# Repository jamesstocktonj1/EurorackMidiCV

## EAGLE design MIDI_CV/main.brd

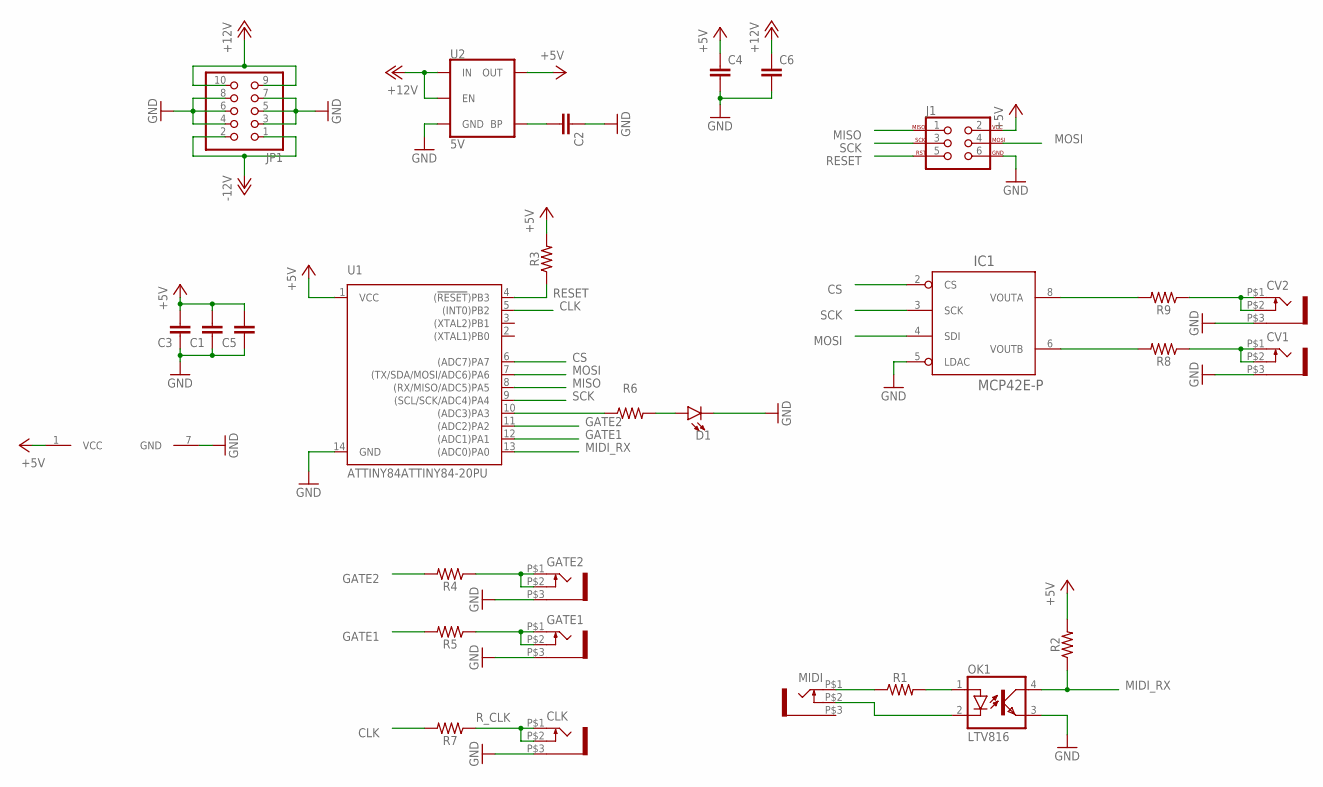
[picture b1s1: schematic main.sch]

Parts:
C1, C2, C3, C5: CAP-0603; 0603
C4, C6: CAP-0805; 0805
CLK: WQP-PJ301M-12_JACK
CV1, CV2: WQP-PJ301M-12_JACK
D1: LED3MM; LED_3MM
GATE1, GATE2: WQP-PJ301M-12_JACK
IC1: MCP42E-P; DIL08
J1: AVR_SPI_PROG_3X2PTH; 2X3
JP1: PINHD-2X5; 2X05
MIDI: WQP-PJ301M-12_JACK
OK1: LTV816; DIL04
R1, R2: AXIAL-0.3
R3, R4, R5, R6, R7, R8, R9: 0603
U1: ATTINY84ATTINY84-20PU; DIP14
U2: 5V; SOT23-5

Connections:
+5V: C1.2, C3.2, C4.1, C5.2, IC1.1 (VCC), J1.2, R2.P$2 (2), R3.2, U1.1 (VCC), U2.5 (OUT)
+12V: C6.1, JP1.9, JP1.10, U2.1 (IN), U2.3 (EN)
-12V: JP1.1, JP1.2
CLK: R7.2, U1.5 ((INT0)PB2)
CS: IC1.2 (CS), U1.6 ((ADC7)PA7)
GATE1: R5.2, U1.12 ((ADC1)PA1)
GATE2: R4.2, U1.11 ((ADC2)PA2)
GND: C1.1, C2.1, C3.1, C4.2, C5.1, C6.2, CLK.P$3 (1), CV1.P$3 (1), CV2.P$3 (1), D1.K (C), GATE1.P$3 (1), GATE2.P$3 (1), IC1.5 (LDAC), IC1.7 (GND), J1.6, JP1.3, JP1.4, JP1.5, JP1.6, JP1.7, JP1.8, OK1.3 (EMIT), U1.14 (GND), U2.2 (GND)
MIDI_RX: OK1.4 (COL), R2.P$1 (1), U1.13 ((ADC0)PA0)
MISO: J1.1, U1.8 ((RX/MISO/ADC5)PA5)
MOSI: IC1.4 (SDI), J1.4, U1.7 ((TX/SDA/MOSI/ADC6)PA6)
unnamed: MIDI.P$1 (2), R1.P$1 (1)
unnamed: OK1.1 (A), R1.P$2 (2)
unnamed: MIDI.P$2 (3), OK1.2 (C)
unnamed: IC1.8 (VOUTA), R9.2
unnamed: IC1.6 (VOUTB), R8.2
unnamed: CV1.P$1 (2), CV1.P$2 (3), R8.1
unnamed: R6.1, U1.10 ((ADC3)PA3)
unnamed: D1.A, R6.2
unnamed: C2.2, U2.4 (BP)
unnamed: CV2.P$1 (2), CV2.P$2 (3), R9.1
RESET: J1.5, R3.1, U1.4 ((!RESET!)PB3)
R_CLK: CLK.P$1 (2), CLK.P$2 (3), R7.1
R_GATE1: GATE1.P$1 (2), GATE1.P$2 (3), R5.1
R_GATE2: GATE2.P$1 (2), GATE2.P$2 (3), R4.1
SCK: IC1.3 (SCK), J1.3, U1.9 ((SCL/SCK/ADC4)PA4)

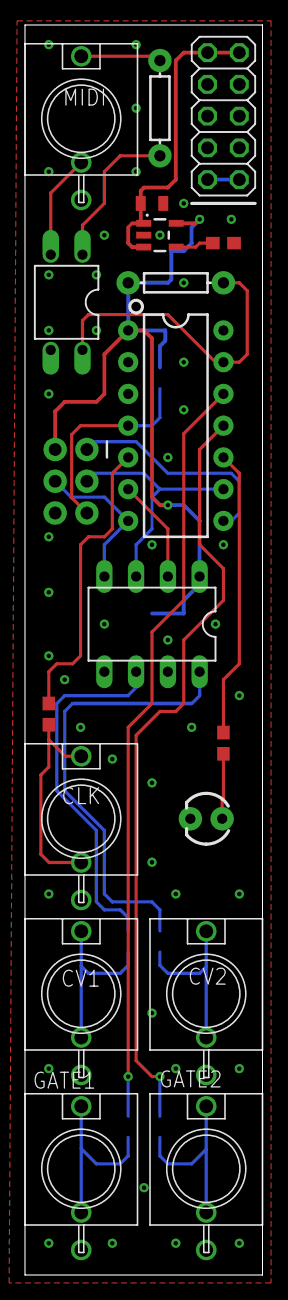
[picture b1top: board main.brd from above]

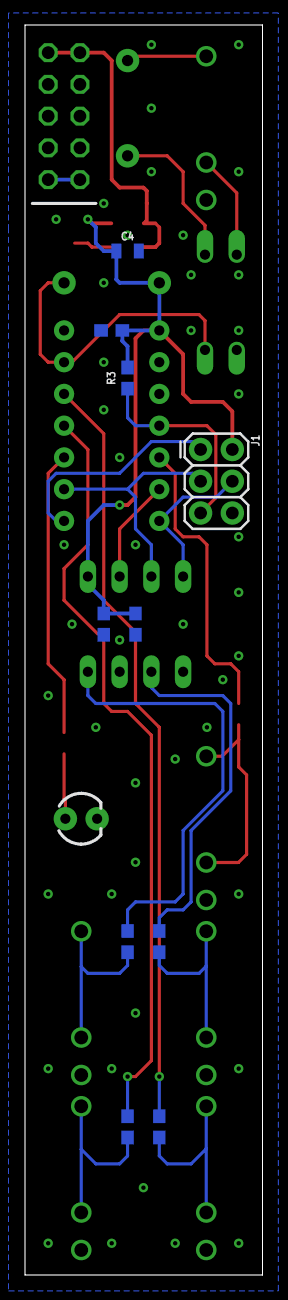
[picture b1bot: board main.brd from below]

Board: 2 copper layers, 19.0 x 100.0 mm, 28 parts (10 on the bottom side), 26 nets.

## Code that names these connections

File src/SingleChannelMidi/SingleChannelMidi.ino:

#include <SoftwareSerial.h>
#include "dac.h"
#include <MIDI.h>


//pin constants
#define MIDI_TX 10
#define MIDI_RX 0
#define LED 3

#define GATE1 1
#define GATE2 2
#define CLK 8
#define CLK_LED 3

#define CLK_PULSE 10
#define CLK_LED_PULSE 50
#define CLK_LED_DIVIDE 4


//dac / midi constants
#define startVoltage 0
#define endVoltage 4000
#define voltageRange (endVoltage - startVoltage)

#define startNote 24
#define endNote 72
#define noteRange (endNote - startNote)


Dac dac;
SoftwareSerial serialMidi(MIDI_RX, MIDI_TX);

byte bufIn[3];

uint8_t curNote = 0;

bool clockEnable = false;
uint8_t clockCount = 0;
uint32_t gateTime = 0;
uint32_t ledTime = 0;





void midiNoteOn(byte channel, byte pitch, byte velocity);
void midiNoteOff(byte channel, byte pitch, byte velocity);

void handleClockPulse(void);
void handleStartClock(void);
void handleStopClock(void);

void setup() {
  pinMode(LED, OUTPUT);

  pinMode(GATE1, OUTPUT);
  pinMode(GATE2, OUTPUT);

  serialMidi.begin(31250);

  dac.initDac();

  dac.writeChannelA(0);
  dac.writeChannelB(0);
}


void loop() {

  if(serialMidi.available() > 0) {
    bufIn[0] = serialMidi.read();
    
    switch(bufIn[0]) {
      case 0xF8:
        handleClockPulse();
        break;
      case 0xFA:
        handleStartClock();
        break;
      case 0xFB:
        handleStartClock();
        break;
      case 0xFC:
        handleStopClock();
        break;
      default:
        while(serialMidi.available() < 2);
        bufIn[1] = serialMidi.read();
        bufIn[2] = serialMidi.read();
        if((bufIn[0] >> 4) == 0x8) {
          midiNoteOff(bufIn[0] & 0x0F, bufIn[1], bufIn[2]);
        }
        else if((bufIn[0] >> 4) == 0x9) {
          midiNoteOn(bufIn[0] & 0x0F, bufIn[1], bufIn[2]);
        }
        //digitalWrite(LED, HIGH);
        //delay(5);
        //digitalWrite(LED, LOW);
        break;
    }
  }
  
  digitalWrite(CLK, (millis() < gateTime) && clockEnable);
  digitalWrite(CLK_LED, millis() < ledTime);
}

void handleClockPulse() {

  //every quarter beat
  if((clockCount % 24) == 0) {
    ledTime = (clockEnable) ? (millis() + CLK_LED_PULSE) : ledTime;
  }

  //every sixteenth
  if((clockCount % 6) == 0) {
    gateTime = millis() + CLK_PULSE;
  }

  clockCount = (clockCount == 23) ? 0 : clockCount + 1;
}

void handleStartClock() {
  clockCount = 0;
  clockEnable = true;
}

void handleStopClock() {
  clockEnable = false;
}


void midiNoteOn(byte channel, byte pitch, byte velocity) {

  if((startNote <= pitch <= endNote) && (channel == 0)) {
  //if((pitch >= startNote) && (pitch <= endNote) && (channel == 0)) {
    digitalWrite(GATE2, HIGH);
    ledTime = millis() + CLK_LED_PULSE;
    
    dac.writeChannelA((pitch - startNote) * (voltageRange / noteRange));
    curNote = pitch;
  }
}

void midiNoteOff(byte channel, byte pitch, byte velocity) {

  if(channel == 0) {
    digitalWrite(GATE2, LOW);
  }
}

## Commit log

2022-01-27 Hardware Push
2022-01-27 Simple Code
2022-01-27 Images Upload

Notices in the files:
parts and their libraries:
SparkFun-Capacitors: Licensing: Creative Commons ShareAlike 4.0 International - https://creativecommons.org/licenses/by-sa/4.0
